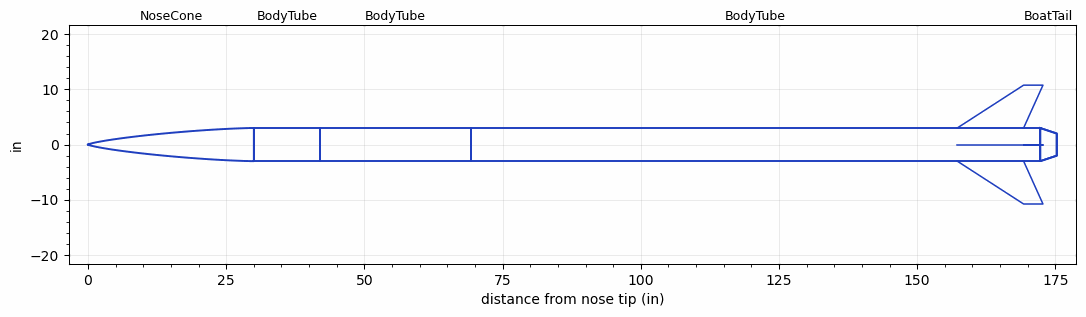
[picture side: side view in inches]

<RASAeroDocument>
 <FileVersion>2</FileVersion>
 <RocketDesign>
  <NoseCone>
   <Length>29.9999</Length>
   <Diameter>6</Diameter>
   <Shape>Von Karman Ogive</Shape>
   <Location>0</Location>
  </NoseCone>
  <BodyTube>
   <Length>12</Length>
   <Diameter>6</Diameter>
   <Location>29.9999</Location>
  </BodyTube>
  <BodyTube>
   <Length>27.2579</Length>
   <Diameter>6</Diameter>
   <Location>41.9999</Location>
  </BodyTube>
  <BodyTube>
   <Length>102.9998</Length>
   <Diameter>6</Diameter>
   <Location>69.2578</Location>
   <BoattailLength>3</BoattailLength>
   <BoattailRearDiameter>4</BoattailRearDiameter>
   <Fin>
    <Count>4</Count>
    <Chord>12</Chord>
    <Span>7.75</Span>
    <SweepDistance>12</SweepDistance>
    <TipChord>3.5</TipChord>
    <Thickness>0.3</Thickness>
    <LERadius>0.1</LERadius>
    <Location>15</Location>
    <AirfoilSection>Double Wedge</AirfoilSection>
    <FX1>6</FX1>
   </Fin>
  </BodyTube>
  <BoatTail>
   <Length>3</Length>
   <Diameter>6</Diameter>
   <RearDiameter>4</RearDiameter>
   <Location>172.2576</Location>
  </BoatTail>
  <Surface>Camouflage Paint</Surface>
  <ModifiedBarrowman>False</ModifiedBarrowman>
  <Turbulence>False</Turbulence>
  <UseBooster1>False</UseBooster1>
  <UseBooster2>False</UseBooster2>
  <Comments>2027 IREC rocket Preliminary design - 9/11/2026</Comments>
 </RocketDesign>
 <LaunchSite>
  <Altitude>0</Altitude>
  <Pressure>27.0701</Pressure>
  <RodAngle>8</RodAngle>
  <RodLength>32.8</RodLength>
  <Temperature>76</Temperature>
  <WindSpeed>18</WindSpeed>
 </LaunchSite>
 <Recovery>
  <Altitude1>0</Altitude1>
  <Altitude2>0</Altitude2>
  <DeviceType1>None</DeviceType1>
  <DeviceType2>None</DeviceType2>
  <Event1>False</Event1>
  <Event2>False</Event2>
  <Size1>0</Size1>
  <Size2>0</Size2>
  <EventType1>None</EventType1>
  <EventType2>None</EventType2>
  <CD1>0</CD1>
  <CD2>0</CD2>
 </Recovery>
 <SimulationList>
  <Simulation>
   <SustainerEngine>ENGINE-2027-python-og  (TAMUSRT)</SustainerEngine>
   <SustainerLaunchWt>134.38</SustainerLaunchWt>
   <SustainerNozzleDiameter>4</SustainerNozzleDiameter>
   <SustainerCG>102.42</SustainerCG>
   <SustainerIgnitionDelay>0</SustainerIgnitionDelay>
   <Booster1SeparationDelay>0</Booster1SeparationDelay>
   <Booster1IgnitionDelay>0</Booster1IgnitionDelay>
   <IncludeBooster1>False</IncludeBooster1>
   <Booster2Delay>0</Booster2Delay>
   <IncludeBooster2>False</IncludeBooster2>
   <TimetoApogee>44.27858</TimetoApogee>
   <MaxAltitude>30986.09</MaxAltitude>
   <MaxVelocity>1884.643</MaxVelocity>
  </Simulation>
  <Simulation>
   <SustainerEngine>ENGINE-2027-python-BOX2500N  (TAMUSRT)</SustainerEngine>
   <SustainerLaunchWt>134.38</SustainerLaunchWt>
   <SustainerNozzleDiameter>4</SustainerNozzleDiameter>
   <SustainerCG>102.42</SustainerCG>
   <SustainerIgnitionDelay>0</SustainerIgnitionDelay>
   <Booster1SeparationDelay>0</Booster1SeparationDelay>
   <Booster1IgnitionDelay>0</Booster1IgnitionDelay>
   <IncludeBooster1>False</IncludeBooster1>
   <Booster2Delay>0</Booster2Delay>
   <IncludeBooster2>False</IncludeBooster2>
   <TimetoApogee>44.58852</TimetoApogee>
   <MaxAltitude>28059.27</MaxAltitude>
   <MaxVelocity>1781.39</MaxVelocity>
  </Simulation>
  <Simulation>
   <SustainerEngine>ENGINE-2027-python-BOX3000N  (TAMUSRT)</SustainerEngine>
   <SustainerLaunchWt>134.38</SustainerLaunchWt>
   <SustainerNozzleDiameter>4</SustainerNozzleDiameter>
   <SustainerCG>102.42</SustainerCG>
   <SustainerIgnitionDelay>0</SustainerIgnitionDelay>
   <Booster1SeparationDelay>0</Booster1SeparationDelay>
   <Booster1IgnitionDelay>0</Booster1IgnitionDelay>
   <IncludeBooster1>False</IncludeBooster1>
   <Booster2Delay>0</Booster2Delay>
   <IncludeBooster2>False</IncludeBooster2>
   <TimetoApogee>44.76849</TimetoApogee>
   <MaxAltitude>30140.07</MaxAltitude>
   <MaxVelocity>1836.142</MaxVelocity>
  </Simulation>
  <Simulation>
   <SustainerEngine>ENGINE-2027-python-BOX3500N  (TAMUSRT)</SustainerEngine>
   <SustainerLaunchWt>134.38</SustainerLaunchWt>
   <SustainerNozzleDiameter>4</SustainerNozzleDiameter>
   <SustainerCG>102.42</SustainerCG>
   <SustainerIgnitionDelay>0</SustainerIgnitionDelay>
   <Booster1SeparationDelay>0</Booster1SeparationDelay>
   <Booster1IgnitionDelay>0</Booster1IgnitionDelay>
   <IncludeBooster1>False</IncludeBooster1>
   <Booster2Delay>0</Booster2Delay>
   <IncludeBooster2>False</IncludeBooster2>
   <TimetoApogee>44.49854</TimetoApogee>
   <MaxAltitude>31082.7</MaxAltitude>
   <MaxVelocity>1884.822</MaxVelocity>
  </Simulation>
  <Simulation>
   <SustainerEngine>ENGINE-2027-python-BOX4000N  (TAMUSRT)</SustainerEngine>
   <SustainerLaunchWt>134.38</SustainerLaunchWt>
   <SustainerNozzleDiameter>4</SustainerNozzleDiameter>
   <SustainerCG>102.42</SustainerCG>
   <SustainerIgnitionDelay>0</SustainerIgnitionDelay>
   <Booster1SeparationDelay>0</Booster1SeparationDelay>
   <Booster1IgnitionDelay>0</Booster1IgnitionDelay>
   <IncludeBooster1>False</IncludeBooster1>
   <Booster2Delay>0</Booster2Delay>
   <IncludeBooster2>False</IncludeBooster2>
   <TimetoApogee>44.1186</TimetoApogee>
   <MaxAltitude>31531.41</MaxAltitude>
   <MaxVelocity>1924.828</MaxVelocity>
  </Simulation>
  <Simulation>
   <SustainerEngine>ENGINE-2027-python-BOX4500N  (TAMUSRT)</SustainerEngine>
   <SustainerLaunchWt>134.38</SustainerLaunchWt>
   <SustainerNozzleDiameter>4</SustainerNozzleDiameter>
   <SustainerCG>102.42</SustainerCG>
   <SustainerIgnitionDelay>0</SustainerIgnitionDelay>
   <Booster1SeparationDelay>0</Booster1SeparationDelay>
   <Booster1IgnitionDelay>0</Booster1IgnitionDelay>
   <IncludeBooster1>False</IncludeBooster1>
   <Booster2Delay>0</Booster2Delay>
   <IncludeBooster2>False</IncludeBooster2>
   <TimetoApogee>43.73867</TimetoApogee>
   <MaxAltitude>31750.1</MaxAltitude>
   <MaxVelocity>1960.239</MaxVelocity>
  </Simulation>
 </SimulationList>
</RASAeroDocument>
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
